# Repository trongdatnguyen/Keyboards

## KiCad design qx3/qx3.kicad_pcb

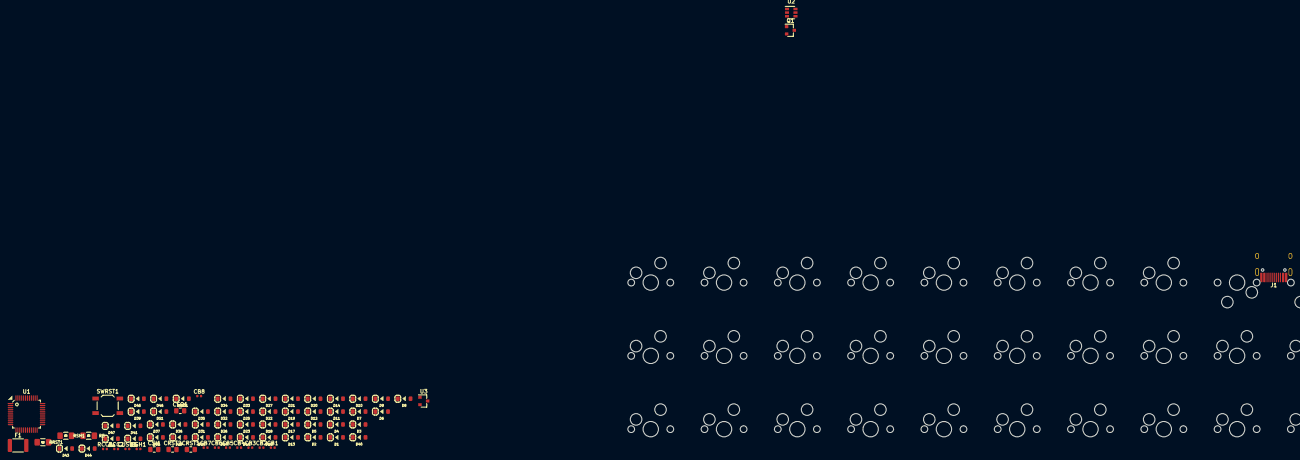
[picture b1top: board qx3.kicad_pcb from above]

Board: 2 copper layers, 121 parts (0 on the bottom side), 73 nets, no tracks yet.

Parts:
CB1: 1uF; C_0402_1005Metric
CB2: 10n; C_0402_1005Metric
CB3, CB5, CB8: 100n; C_0402_1005Metric
CB4, CB6: 4.7uF; C_0402_1005Metric
CB7: 100nF; C_0402_1005Metric
CRST1: 100uF; C_0805_2012Metric_Pad1.15x1.40mm_HandSolder
CRST2: 4.7nF; C_0805_2012Metric_Pad1.15x1.40mm_HandSolder
CSH1: 4.7nF; C_0402_1005Metric
CSI1: 10n; C_0805_2012Metric_Pad1.15x1.40mm_HandSolder
CSO1: 1u; C_0805_2012Metric_Pad1.15x1.40mm_HandSolder
CUSB1: 100n; C_0402_1005Metric
D1, D2, D3, D4, D5, D6, D7, D8, D9, D10, D11, D12, D13, D14, D15, D16, D17, D18, D19, D20, D21, D22, D23, D24, D25, D26, D27, D28, D29, D30, D31, D32, D33, D34, D35, D36, D37, D38, D39, D40, D41, D42, D43, D44, D45, D46: 1N4148; D_SOD-123
D47: D_TVS; D_SOD-123
DRST1: 1N4148; D_SOD-123
DS1: 1N4148; D_SOD-123
F1: Polyfuse_Small; Fuse_1812_4532
J1: TYPE-C-31-M12_13; HRO-TYPE-C-31-M-12-HandSoldering
Q1: DTC123J; SOT-23
R5: 33kO; R_SMD_1206
RCC1, RCC2: 5.1k; R_0402_1005Metric
RRST1: 100k; R_SMD_1206
RSH1: 1M; R_SMD_1206
SW1: SHIFT▲; MXOnly-1.5U-Hotswap
SW2: CHAR; MXOnly-1U-Hotswap
SW3: ENTER; MXOnly-4U-Hotswap
SW4: JOB COMMAND; MXOnly-1.5U-Hotswap
SW5: ◀; MXOnly-1U-Hotswap
SW6: ▶; MXOnly-1U-Hotswap
SW7: INS; MXOnly-1U-Hotswap
SW8: (; MXOnly-1U-Hotswap
SW9: ); MXOnly-1U-Hotswap
SW10: .; MXOnly-1U-Hotswap
SW11: _; MXOnly-1U-Hotswap
SW12: !; MXOnly-1U-Hotswap
SW13: ?; MXOnly-1U-Hotswap
SW14: &; MXOnly-1U-Hotswap
SW15: F1; MXOnly-1U-Hotswap
SW16: F2; MXOnly-1U-Hotswap
SW17: U; MXOnly-1U-Hotswap
SW18: V; MXOnly-1U-Hotswap
SW19: W; MXOnly-1U-Hotswap
SW20: X; MXOnly-1U-Hotswap
SW21: Y; MXOnly-1U-Hotswap
SW22: Z; MXOnly-1U-Hotswap
SW23: +; MXOnly-1U-Hotswap
SW24: -; MXOnly-1U-Hotswap
SW25: *; MXOnly-1U-Hotswap
SW26: /; MXOnly-1U-Hotswap
SW27: K; MXOnly-1U-Hotswap
SW28: L; MXOnly-1U-Hotswap
SW29: M; MXOnly-1U-Hotswap
SW30: N; MXOnly-1U-Hotswap
SW31: O; MXOnly-1U-Hotswap
SW32: P; MXOnly-1U-Hotswap
SW33: Q; MXOnly-1U-Hotswap
SW34: R; MXOnly-1U-Hotswap
SW35: S; MXOnly-1U-Hotswap
SW36: T; MXOnly-1U-Hotswap
SW37: A; MXOnly-1U-Hotswap
SW38: B; MXOnly-1U-Hotswap
SW39: C; MXOnly-1U-Hotswap
SW40: D; MXOnly-1U-Hotswap
SW41: E; MXOnly-1U-Hotswap
SW42: F; MXOnly-1U-Hotswap
SW43: G; MXOnly-1U-Hotswap
SW44: H; MXOnly-1U-Hotswap
SW45: I; MXOnly-1U-Hotswap
SW46: J; MXOnly-1U-Hotswap
SWRST1: SW_PUSH; SW_SPST_TL3342
U1: STM32F072-LQFP48; LQFP-48_7x7mm_P0.5mm
U2: USBLC6-2SC6; SOT-23-6
U3: MCP1700-3302E_SOT23; SOT-23

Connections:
3.3V: CB1.2, CB2.2, CB3.2, CB4.2, CB5.2, CB6.2, CB7.2, CB8.2, U1.1, U1.9, U1.24, U1.36, U1.48
5V: CSI1.1, D47.1, DS1.1, F1.1, U3.3
+3V3: CSO1.1, DS1.2, SWRST1.1, U3.2
BOOT0: CRST1.1, R5.1, RRST1.1, U1.44
Col1: SW1.1, SW7.1, SW17.1, SW27.1, SW37.1, U1.13
Col2: SW2.1, SW8.1, SW18.1, SW28.1, SW38.1, U1.14
Col3: SW9.1, SW19.1, SW29.1, SW39.1, U1.15
Col4: SW10.1, SW20.1, SW30.1, SW40.1, U1.16
Col5: SW11.1, SW21.1, SW31.1, SW41.1, U1.17
Col6: SW3.1, SW12.1, SW22.1, SW32.1, SW42.1, U1.18
Col7: SW13.1, SW23.1, SW33.1, SW43.1, U1.19
Col8: SW4.1, SW14.1, SW24.1, SW34.1, SW44.1, U1.20
Col9: SW5.1, SW15.1, SW25.1, SW35.1, SW45.1, U1.21
Col10: SW6.1, SW16.1, SW26.1, SW36.1, SW46.1, U1.22
D+: U1.33, U2.3
D-: U1.32, U2.1
GND: CB1.1, CB2.1, CB3.1, CB4.1, CB5.1, CB6.1, CB7.1, CB8.1, CRST1.2, CRST2.1, CSH1.2, CSI1.2, CSO1.2, CUSB1.1, D47.2, Q1.2, RCC1.1, RCC2.1, RRST1.2, RSH1.2, U1.8, U1.23, U1.35, U1.47, U2.2, U3.1
NRST: CRST2.2, Q1.3, U1.7
unnamed: CSH1.1, RSH1.1
unnamed: D1.2, SW1.2
unnamed: D2.2, SW2.2
unnamed: D3.2, SW3.2
unnamed: D4.2, SW4.2
unnamed: D5.2, SW5.2
unnamed: D6.2, SW6.2
unnamed: D7.2, SW7.2
unnamed: D8.2, SW8.2
unnamed: D9.2, SW9.2
unnamed: D10.2, SW10.2
unnamed: D11.2, SW11.2
unnamed: D12.2, SW12.2
unnamed: D13.2, SW13.2
unnamed: D14.2, SW14.2
unnamed: D15.2, SW15.2
unnamed: D16.2, SW16.2
unnamed: D17.2, SW17.2
unnamed: D18.2, SW18.2
unnamed: D19.2, SW19.2
unnamed: D20.2, SW20.2
unnamed: D21.2, SW21.2
unnamed: D22.2, SW22.2
unnamed: D23.2, SW23.2
unnamed: D24.2, SW24.2
unnamed: D25.2, SW25.2
unnamed: D26.2, SW26.2
unnamed: D27.2, SW27.2
unnamed: D28.2, SW28.2
unnamed: D29.2, SW29.2
unnamed: D30.2, SW30.2
unnamed: D31.2, SW31.2
unnamed: D32.2, SW32.2
unnamed: D33.2, SW33.2
unnamed: D34.2, SW34.2
unnamed: D35.2, SW35.2
unnamed: D36.2, SW36.2
unnamed: D37.2, SW37.2
unnamed: D38.2, SW38.2
unnamed: D39.2, SW39.2
unnamed: D40.2, SW40.2
unnamed: D41.2, SW41.2
unnamed: D42.2, SW42.2
unnamed: D43.2, SW43.2
unnamed: D44.2, SW44.2
unnamed: D45.2, SW45.2
unnamed: D46.2, SW46.2
unnamed: DRST1.1, R5.2
unnamed: DRST1.2, Q1.1, SWRST1.2
Row1: D1.1, D2.1, D3.1, D4.1, D5.1, D6.1, U1.2
Row2: D7.1, D8.1, D9.1, D10.1, D11.1, D12.1, D13.1, D14.1, D15.1, D16.1, U1.3
Row3: D17.1, D18.1, D19.1, D20.1, D21.1, D22.1, D23.1, D24.1, D25.1, D26.1, U1.4
Row4: D27.1, D28.1, D29.1, D30.1, D31.1, D32.1, D33.1, D34.1, D35.1, D36.1, U1.5
Row5: D37.1, D38.1, D39.1, D40.1, D41.1, D42.1, D43.1, D44.1, D45.1, D46.1, U1.6
VBUS: CUSB1.2, F1.2, U2.5

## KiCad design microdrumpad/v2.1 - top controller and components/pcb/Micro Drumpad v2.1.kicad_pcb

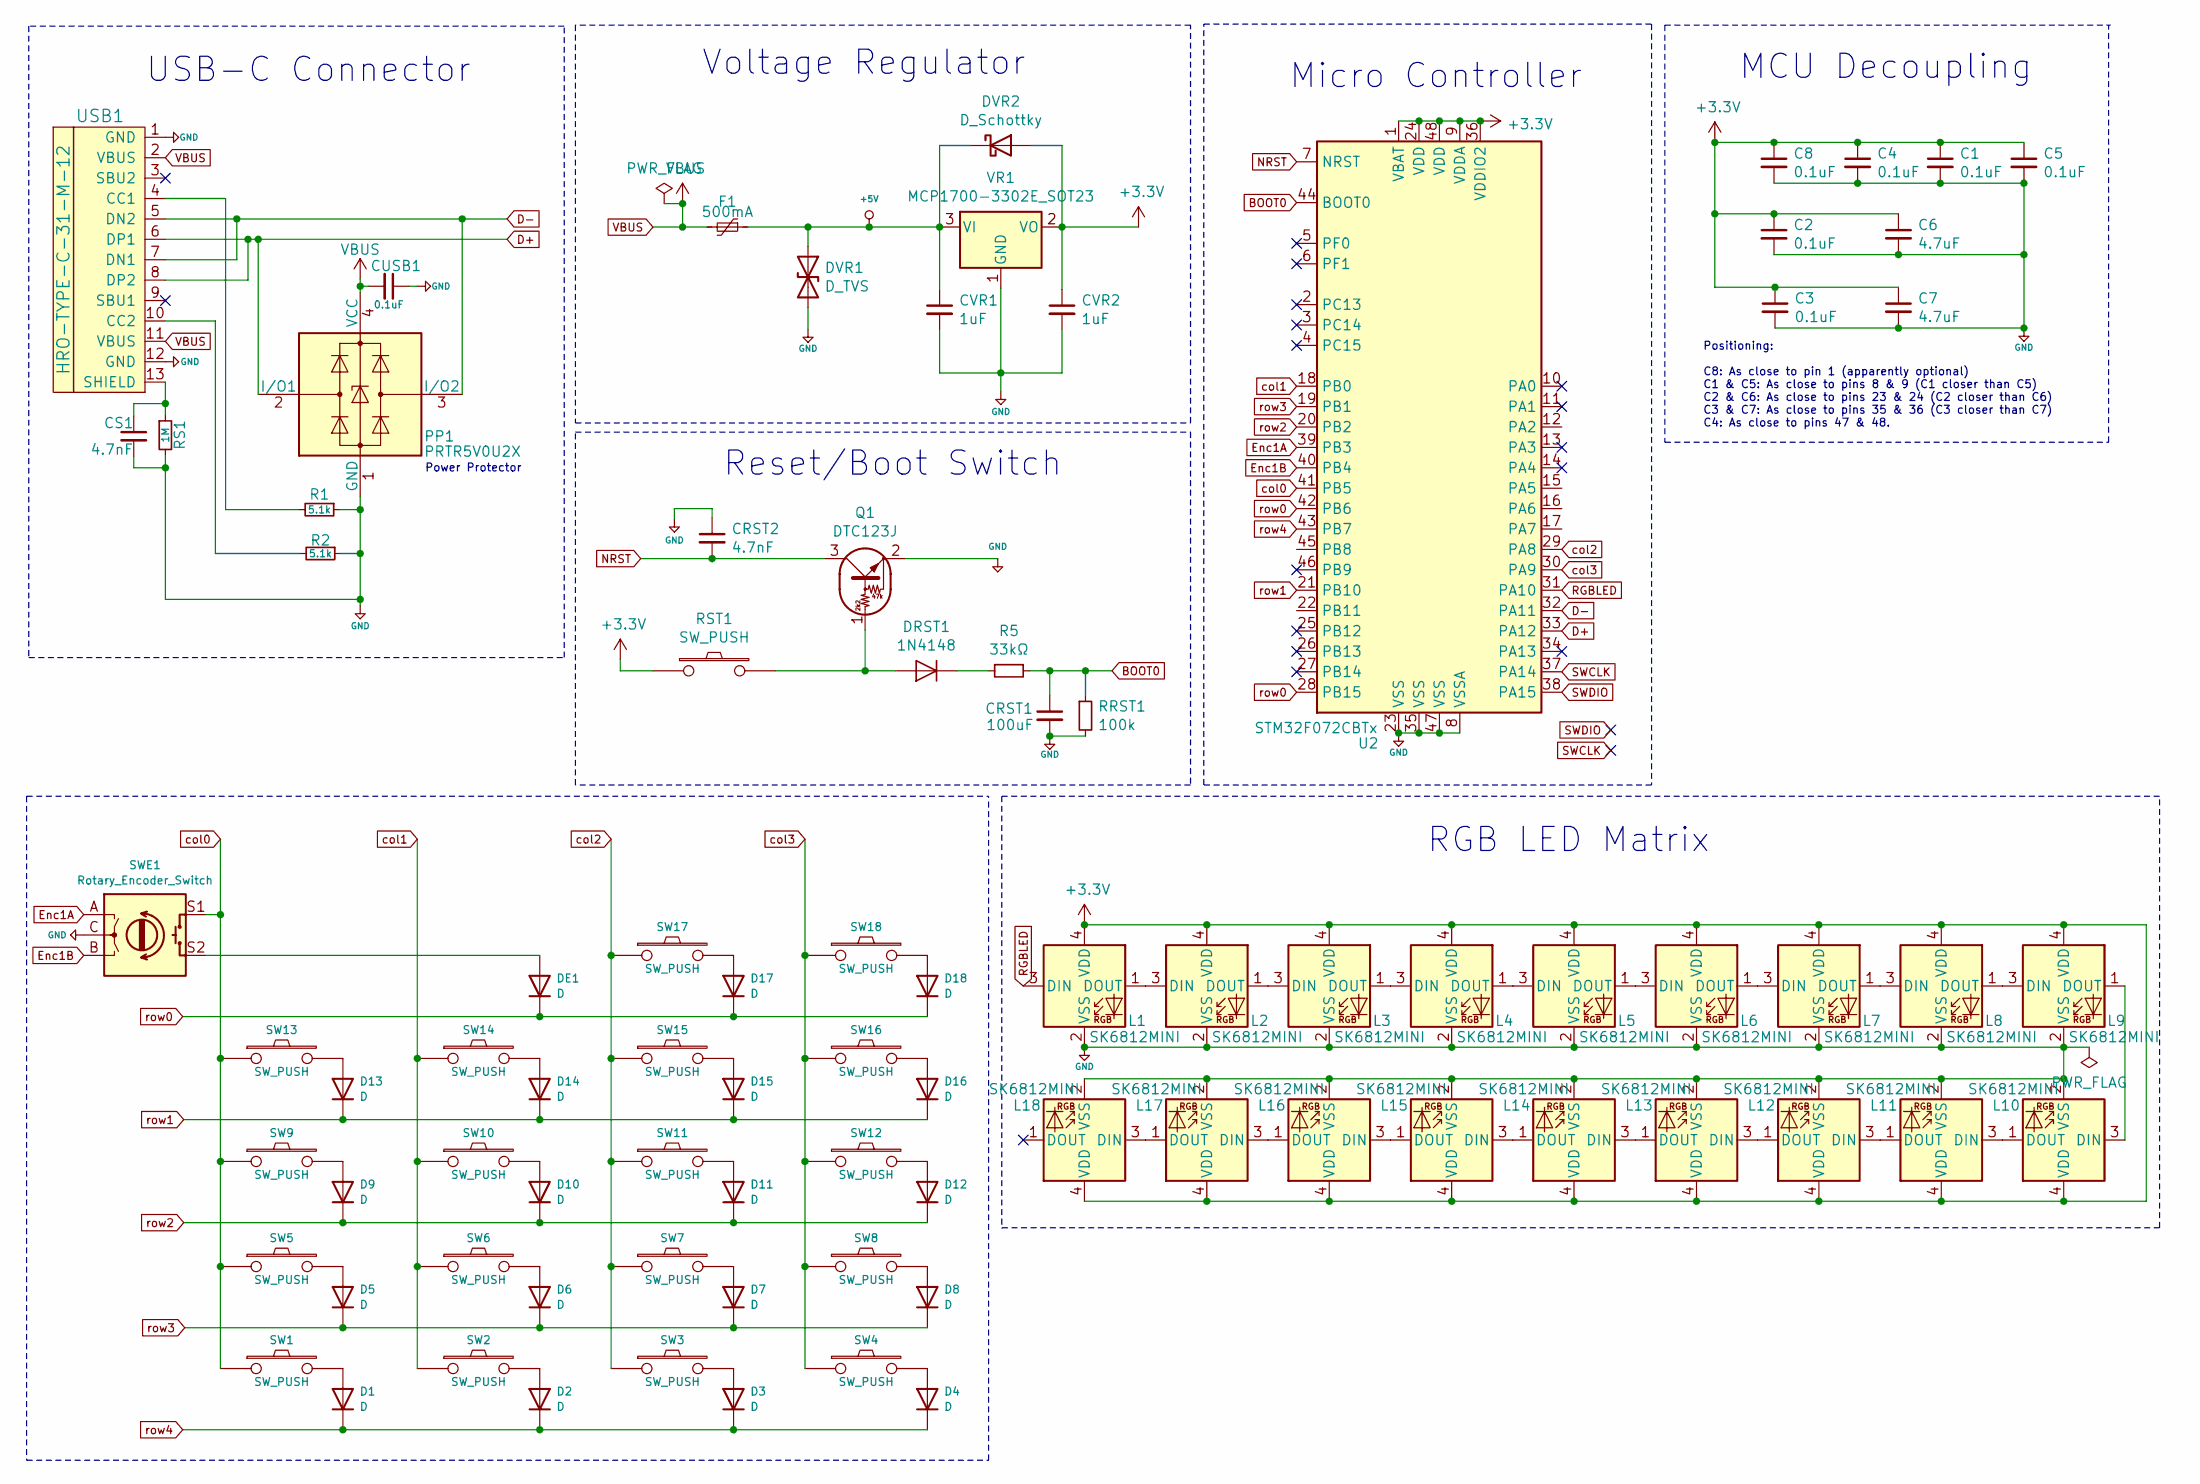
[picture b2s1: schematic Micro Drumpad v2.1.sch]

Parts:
C1, C2, C3, C4, C5, C8: 0.1uF; C_0805_2012Metric
C6, C7: 4.7uF; C_0805_2012Metric
CRST1: 100uF; C_0805_2012Metric
CRST2: 4.7nF; C_0805_2012Metric
CS1: 4.7nF; C_0805_2012Metric
CUSB1: 0.1uF; C_0805_2012Metric
CVR1, CVR2: 1uF; C_0805_2012Metric
D1, D2, D3, D4, D5, D6, D7, D8, D9, D10, D11, D12, D13, D14, D15, D16, D17, D18: D; D_SOD-123
DE1: D; D_SOD-123
DRST1: 1N4148; D_DO-35_SOD27_P7.62mm_Horizontal
DVR1: D_TVS; D_SOD-123
DVR2: D_Schottky; D_SOD-123
F1: 500mA; Fuse_1206_3216Metric
L1, L2, L3, L4, L5, L6, L7, L8, L9, L10, L11, L12, L13, L14, L15, L16, L17, L18: SK6812MINI; LED_SK6812MINI_PLCC4_3.5x3.5mm_P1.75mm
PP1: PRTR5V0U2X; SOT-143
Q1: DTC123J; SOT-23
R1, R2: 5.1k; R_0805_2012Metric
R5: 33kΩ; R_0805_2012Metric
RRST1: 100k; R_0805_2012Metric
RS1: 1M; R_0805_2012Metric
RST1: SW_PUSH; SW_SPST_TL3342
SW1, SW2, SW3, SW4, SW5, SW6, SW7, SW8, SW9, SW10, SW11, SW12, SW13, SW14, SW15, SW16, SW17, SW18: SW_PUSH; MXOnly-1U-Hotswap
SWE1: Rotary_Encoder_Switch; RotaryEncoder_Alps_EC11E-Switch_Vertical_H20mm
U2: STM32F072CBTx; LQFP-48_7x7mm_P0.5mm
USB1: HRO-TYPE-C-31-M-12
VR1: MCP1700-3302E_SOT23; SOT-23

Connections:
+3V3: C1.1, C2.1, C3.1, C4.1, C5.1, C6.1, C7.1, C8.1, CVR2.1, DVR2.2 (A), L1.4 (VDD), L2.4 (VDD), L3.4 (VDD), L4.4 (VDD), L5.4 (VDD), L6.4 (VDD), L7.4 (VDD), L8.4 (VDD), L9.4 (VDD), L10.4 (VDD), L11.4 (VDD), L12.4 (VDD), L13.4 (VDD), L14.4 (VDD), L15.4 (VDD), L16.4 (VDD), L17.4 (VDD), L18.4 (VDD), RST1.1, U2.1 (VBAT), U2.9 (VDDA), U2.24 (VDD), U2.36 (VDDIO2), U2.48 (VDD), VR1.2 (VO)
BOOT0: CRST1.1, R5.1, RRST1.1, U2.44 (BOOT0)
D+: PP1.2 (I/O1), U2.33 (PA12), USB1.6 (DP1), USB1.8 (DP2)
D-: PP1.3 (I/O2), U2.32 (PA11), USB1.5 (DN2), USB1.7 (DN1)
Enc1A: SWE1.A, U2.39 (PB3)
Enc1B: SWE1.B, U2.40 (PB4)
NRST: CRST2.2, Q1.3 (C), U2.7 (NRST)
unnamed: CS1.1, RS1.1, USB1.13 (SHIELD)
unnamed: D1.2 (A), SW1.2
unnamed: D2.2 (A), SW2.2
unnamed: D3.2 (A), SW3.2
unnamed: D4.2 (A), SW4.2
unnamed: D5.2 (A), SW5.2
unnamed: D6.2 (A), SW6.2
unnamed: D7.2 (A), SW7.2
unnamed: D8.2 (A), SW8.2
unnamed: D9.2 (A), SW9.2
unnamed: D10.2 (A), SW10.2
unnamed: D11.2 (A), SW11.2
unnamed: D12.2 (A), SW12.2
unnamed: D13.2 (A), SW13.2
unnamed: D14.2 (A), SW14.2
unnamed: D15.2 (A), SW15.2
unnamed: D16.2 (A), SW16.2
unnamed: D17.2 (A), SW17.2
unnamed: D18.2 (A), SW18.2
unnamed: DE1.2 (A), SWE1.S2
unnamed: DRST1.1 (K), R5.2
unnamed: DRST1.2 (A), Q1.1 (B), RST1.2
unnamed: L1.1 (DOUT), L2.3 (DIN)
unnamed: L2.1 (DOUT), L3.3 (DIN)
unnamed: L3.1 (DOUT), L4.3 (DIN)
unnamed: L4.1 (DOUT), L5.3 (DIN)
unnamed: L5.1 (DOUT), L6.3 (DIN)
unnamed: L6.1 (DOUT), L7.3 (DIN)
unnamed: L7.1 (DOUT), L8.3 (DIN)
unnamed: L8.1 (DOUT), L9.3 (DIN)
unnamed: L10.1 (DOUT), L11.3 (DIN)
unnamed: L9.1 (DOUT), L10.3 (DIN)
unnamed: L11.1 (DOUT), L12.3 (DIN)
unnamed: L12.1 (DOUT), L13.3 (DIN)
unnamed: L13.1 (DOUT), L14.3 (DIN)
unnamed: L14.1 (DOUT), L15.3 (DIN)
unnamed: L15.1 (DOUT), L16.3 (DIN)
unnamed: L16.1 (DOUT), L17.3 (DIN)
unnamed: L17.1 (DOUT), L18.3 (DIN)
unnamed: R1.2, USB1.4 (CC1)
unnamed: R2.2, USB1.10 (CC2)
RGBLED: L1.3 (DIN), U2.31 (PA10)
SWCLK: U2.37 (PA14)
SWDIO: U2.38 (PA15)
VBUS: CUSB1.2, F1.2, PP1.4 (VCC), USB1.2 (VBUS), USB1.11 (VBUS)
col0: SW1.1, SW5.1, SW9.1, SW13.1, SWE1.S1, U2.41 (PB5)
col1: SW2.1, SW6.1, SW10.1, SW14.1, U2.18 (PB0)
col2: SW3.1, SW7.1, SW11.1, SW15.1, SW17.1, U2.29 (PA8)
col3: SW4.1, SW8.1, SW12.1, SW16.1, SW18.1, U2.30 (PA9)
row0: D17.1 (K), D18.1 (K), DE1.1 (K), U2.28 (PB15), U2.42 (PB6)
row1: D13.1 (K), D14.1 (K), D15.1 (K), D16.1 (K), U2.21 (PB10)
row2: D9.1 (K), D10.1 (K), D11.1 (K), D12.1 (K), U2.20 (PB2)
row3: D5.1 (K), D6.1 (K), D7.1 (K), D8.1 (K), U2.19 (PB1)
row4: D1.1 (K), D2.1 (K), D3.1 (K), D4.1 (K), U2.43 (PB7)

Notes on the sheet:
MCU Decoupling
Reset/Boot Switch
Micro Controller
Positioning: C8: As close to pin 1 (apparently optional) C1 & C5: As close to pins 8 & 9 (C1 closer than C5) C2 & C6: As close to pins 23 & 24 (C2 closer than C6) C3 & C7: As close to pins 35 & 36 (C3 closer than C7) C4: As close to pins 47 & 48.
Voltage Regulator
USB-C Connector
Power Protector
RGB LED Matrix

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
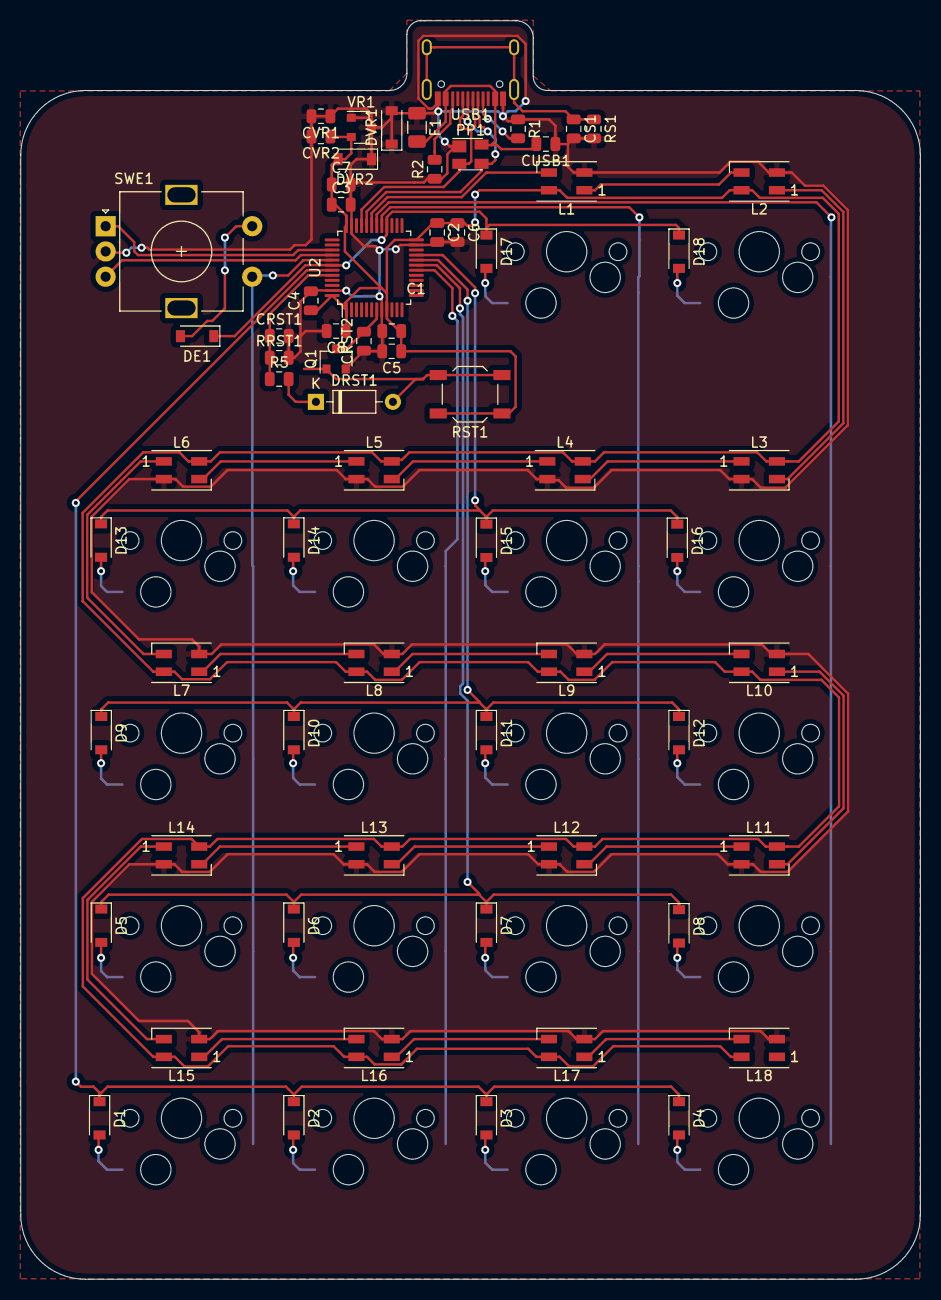
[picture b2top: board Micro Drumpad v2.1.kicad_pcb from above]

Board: 2 copper layers, 89.0 x 124.5 mm, 86 parts (0 on the bottom side), 60 nets.

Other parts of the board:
H1: MountingHole; MountingHole_2.2mm_M2_DIN965

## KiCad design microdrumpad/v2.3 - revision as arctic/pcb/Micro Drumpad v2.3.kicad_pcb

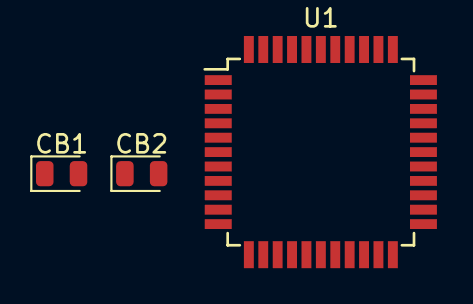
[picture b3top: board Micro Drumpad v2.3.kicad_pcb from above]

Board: 2 copper layers, 3 parts (0 on the bottom side), 2 nets, no tracks yet.

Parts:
CB1, CB2: 10n; D_0805_2012Metric
U1: STM32F072-LQFP48; TQFP-44_10x10mm_P0.8mm

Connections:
3.3V: CB1.2, CB2.2, U1.10
+5V: CB1.1, CB2.1, U1.9

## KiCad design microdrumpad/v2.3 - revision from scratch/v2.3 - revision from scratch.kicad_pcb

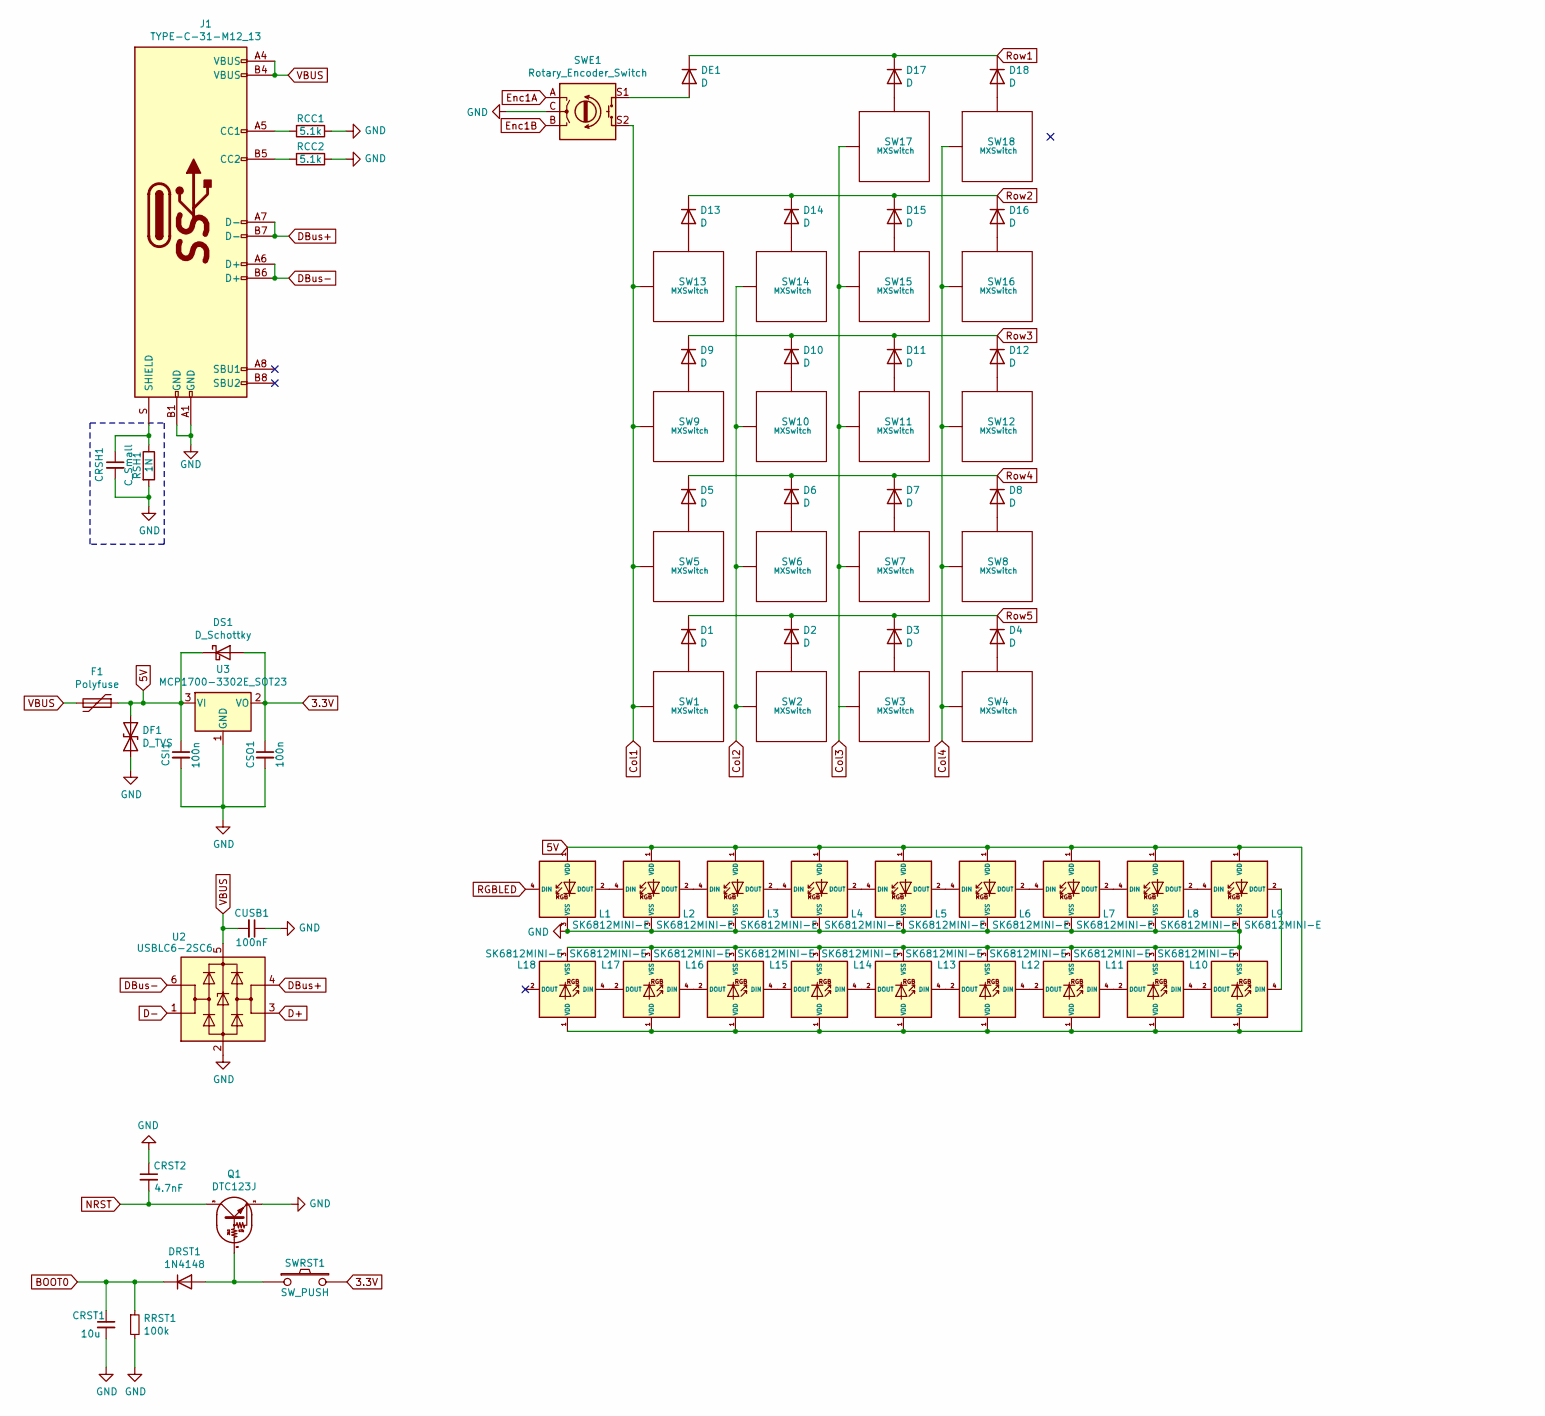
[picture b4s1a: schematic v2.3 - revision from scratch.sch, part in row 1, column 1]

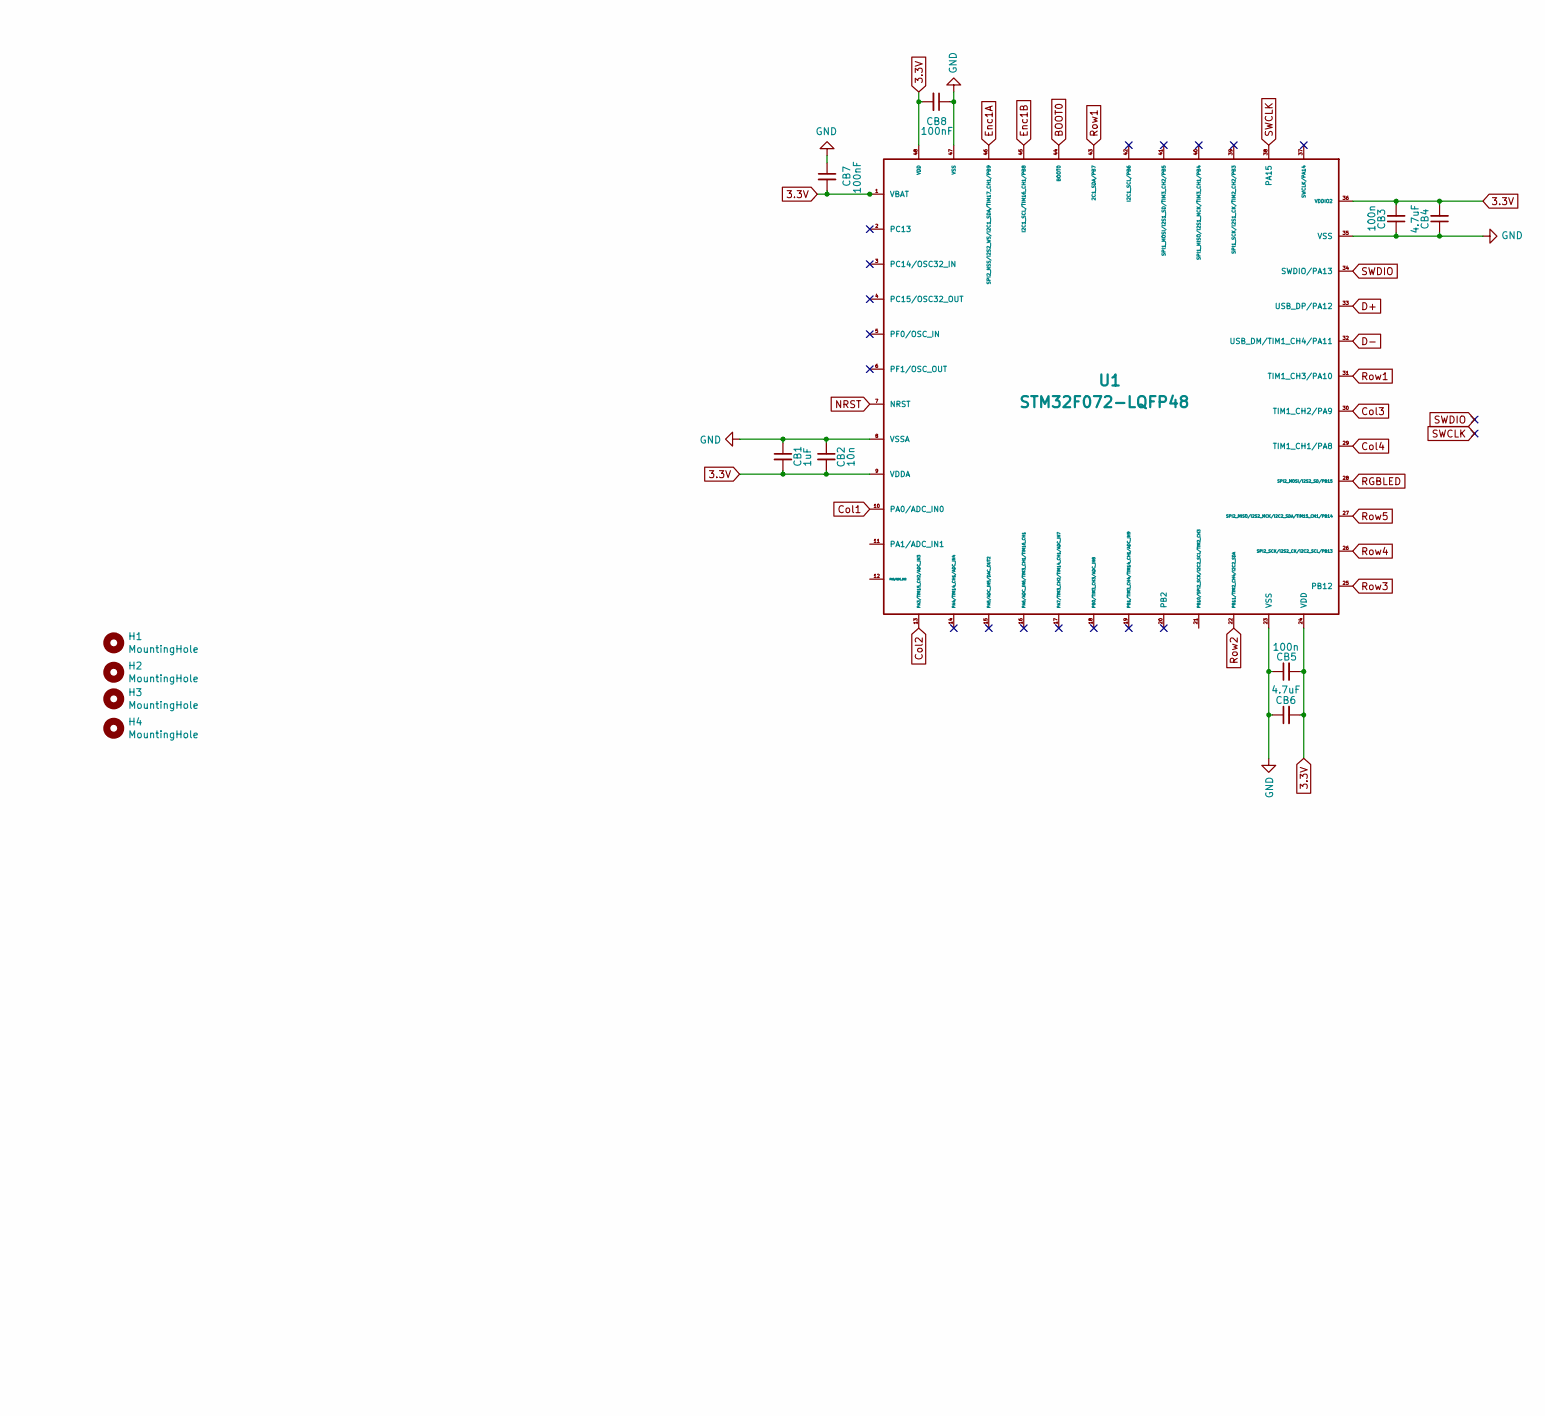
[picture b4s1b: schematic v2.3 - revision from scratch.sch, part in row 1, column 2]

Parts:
CB1: 1uF; C_0805_2012Metric
CB2: 10n; C_0805_2012Metric
CB3, CB5: 100n; C_0805_2012Metric
CB4, CB6: 4.7uF; C_0805_2012Metric
CB7, CB8: 100nF; C_0805_2012Metric
CRSH1: C_Small; C_0805_2012Metric
CRST1: 10u; C_0805_2012Metric
CRST2: 4.7nF; C_0805_2012Metric
CSI1: 100n; C_0805_2012Metric
CSO1: 100n; C_0805_2012Metric
CUSB1: 100nF; D_SOD-123
D1, D2, D3, D4, D5, D6, D7, D8, D9, D10, D11, D12, D13, D14, D15, D16, D17, D18: D; D_SOD-123
DE1: D; D_SOD-123
DF1: D_TVS; D_SOD-123
DRST1: 1N4148; D_DO-35_SOD27_P7.62mm
DS1: D_Schottky; D_SOD-123
F1: Polyfuse; Fuse_0805_2012Metric_Pad1.15x1.40mm_HandSolder
H1: MountingHole; Mounting_Hole_Oval_2.5x8mm
H2: MountingHole; halfSideHole
H3: MountingHole; MoutingHole_Oval_7mm_5.0x2.5mm
H4: MountingHole; MoutingHole_Oval_Poker_7mm_5.0x2.5mm
J1: TYPE-C-31-M12_13; TYPE-C-31-M-12
L1, L2, L3, L4, L5, L6, L7, L8, L9, L10, L11, L12, L13, L14, L15, L16, L17, L18: SK6812MINI-E; SK6812-MINI-E
Q1: DTC123J; SOT-23
RCC1, RCC2: 5.1k; R_SMD_1206
RRST1: 100k; R_SMD_1206
RSH1: 1N; R_SMD_1206
SW1, SW2, SW3, SW4, SW5, SW6, SW7, SW8, SW9, SW10, SW11, SW12, SW13, SW14, SW15, SW16, SW17, SW18: MXSwitch; MXOnly-1U-Hotswap
SWE1: Rotary_Encoder_Switch; RotaryEncoder_Alps_EC11E-Switch_Vertical_H20mm
SWRST1: SW_PUSH; SW_SPST_TL3342
U1: STM32F072-LQFP48; LQFP-48_7x7mm_P0.5mm
U2: USBLC6-2SC6; SOT-23-6
U3: MCP1700-3302E_SOT23; SOT-23

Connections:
3.3V: CB1.2, CB2.2, CB3.2, CB4.2, CB5.2, CB6.2, CB7.2, CB8.2, CSO1.1, DS1.2 (A), SWRST1.2, U1.1 (VBAT), U1.9 (VDDA), U1.24 (VDD), U1.36 (VDDIO2), U1.48 (VDD), U3.2 (VO)
5V: CSI1.1, DF1.2 (A2), DS1.1 (K), F1.1, L1.1 (VDD), L2.1 (VDD), L3.1 (VDD), L4.1 (VDD), L5.1 (VDD), L6.1 (VDD), L7.1 (VDD), L8.1 (VDD), L9.1 (VDD), L10.1 (VDD), L11.1 (VDD), L12.1 (VDD), L13.1 (VDD), L14.1 (VDD), L15.1 (VDD), L16.1 (VDD), L17.1 (VDD), L18.1 (VDD), U3.3 (VI)
BOOT0: CRST1.1, DRST1.1 (K), RRST1.1, U1.44 (BOOT0)
Col1: SW1.1 (Col), SW5.1 (Col), SW9.1 (Col), SW13.1 (Col), SWE1.S2, U1.10 (PA0/ADC_IN0)
Col2: SW2.1 (Col), SW6.1 (Col), SW10.1 (Col), SW14.1 (Col), U1.13 (PA3/TIM15_CH2/ADC_IN3)
Col3: SW3.1 (Col), SW7.1 (Col), SW11.1 (Col), SW15.1 (Col), SW17.1 (Col), U1.30 (TIM1_CH2/PA9)
Col4: SW4.1 (Col), SW8.1 (Col), SW12.1 (Col), SW16.1 (Col), SW18.1 (Col), U1.29 (TIM1_CH1/PA8)
D+: U1.33 (USB_DP/PA12), U2.3 (I/O2)
D-: U1.32 (USB_DM/TIM1_CH4/PA11), U2.1 (I/O1)
DBus+: J1.A7 (D-), J1.B7 (D-), U2.4 (I/O2)
DBus-: J1.A6 (D+), J1.B6 (D+), U2.6 (I/O1)
Enc1A: SWE1.A, U1.46 (SPI2_NSS/I2S2_WS/I2C1_SDA/TIM17_CH1/PB9)
Enc1B: SWE1.B, U1.45 (I2C1_SCL/TIM16_CH1/PB8)
GND: CB1.1, CB2.1, CB3.1, CB4.1, CB5.1, CB6.1, CB7.1, CB8.1, CRSH1.2, CRST1.2, CRST2.1, CSI1.2, CSO1.2, CUSB1.1, DF1.1 (A1), J1.A1 (GND), J1.B1 (GND), L1.3 (VSS), L2.3 (VSS), L3.3 (VSS), L4.3 (VSS), L5.3 (VSS), L6.3 (VSS), L7.3 (VSS), L8.3 (VSS), L9.3 (VSS), L10.3 (VSS), L11.3 (VSS), L12.3 (VSS), L13.3 (VSS), L14.3 (VSS), L15.3 (VSS), L16.3 (VSS), L17.3 (VSS), L18.3 (VSS), Q1.2 (E), RCC1.1, RCC2.1, RRST1.2, RSH1.2, SWE1.C, U1.8 (VSSA), U1.23 (VSS), U1.35 (VSS), U1.47 (VSS), U2.2 (GND), U3.1 (GND)
NRST: CRST2.2, Q1.3 (C), U1.7 (NRST)
unnamed: CRSH1.1, J1.S (SHIELD), RSH1.1
unnamed: D1.2 (A), SW1.2 (Row)
unnamed: D2.2 (A), SW2.2 (Row)
unnamed: D3.2 (A), SW3.2 (Row)
unnamed: D4.2 (A), SW4.2 (Row)
unnamed: D5.2 (A), SW5.2 (Row)
unnamed: D6.2 (A), SW6.2 (Row)
unnamed: D7.2 (A), SW7.2 (Row)
unnamed: D8.2 (A), SW8.2 (Row)
unnamed: D9.2 (A), SW9.2 (Row)
unnamed: D10.2 (A), SW10.2 (Row)
unnamed: D11.2 (A), SW11.2 (Row)
unnamed: D12.2 (A), SW12.2 (Row)
unnamed: D13.2 (A), SW13.2 (Row)
unnamed: D14.2 (A), SW14.2 (Row)
unnamed: D15.2 (A), SW15.2 (Row)
unnamed: D16.2 (A), SW16.2 (Row)
unnamed: D17.2 (A), SW17.2 (Row)
unnamed: D18.2 (A), SW18.2 (Row)
unnamed: DE1.2 (A), SWE1.S1
unnamed: DRST1.2 (A), Q1.1 (B), SWRST1.1
unnamed: J1.A5 (CC1), RCC1.2
unnamed: J1.B5 (CC2), RCC2.2
unnamed: L1.2 (DOUT), L2.4 (DIN)
unnamed: L2.2 (DOUT), L3.4 (DIN)
unnamed: L3.2 (DOUT), L4.4 (DIN)
unnamed: L4.2 (DOUT), L5.4 (DIN)
unnamed: L5.2 (DOUT), L6.4 (DIN)
unnamed: L6.2 (DOUT), L7.4 (DIN)
unnamed: L7.2 (DOUT), L8.4 (DIN)
unnamed: L8.2 (DOUT), L9.4 (DIN)
unnamed: L10.2 (DOUT), L11.4 (DIN)
unnamed: L9.2 (DOUT), L10.4 (DIN)
unnamed: L11.2 (DOUT), L12.4 (DIN)
unnamed: L12.2 (DOUT), L13.4 (DIN)
unnamed: L13.2 (DOUT), L14.4 (DIN)
unnamed: L14.2 (DOUT), L15.4 (DIN)
unnamed: L15.2 (DOUT), L16.4 (DIN)
unnamed: L16.2 (DOUT), L17.4 (DIN)
unnamed: L17.2 (DOUT), L18.4 (DIN)
RGBLED: L1.4 (DIN), U1.28 (SPI2_MOSI/I2S2_SD/PB15)
Row1: D17.1 (K), D18.1 (K), DE1.1 (K), U1.31 (TIM1_CH3/PA10), U1.43 (2C1_SDA/PB7)
Row2: D13.1 (K), D14.1 (K), D15.1 (K), D16.1 (K), U1.22 (PB11/TIM2_CH4/I2C2_SDA)
Row3: D9.1 (K), D10.1 (K), D11.1 (K), D12.1 (K), U1.25 (PB12)
Row4: D5.1 (K), D6.1 (K), D7.1 (K), D8.1 (K), U1.26 (SPI2_SCK/I2S2_CK/I2C2_SCL/PB13)
Row5: D1.1 (K), D2.1 (K), D3.1 (K), D4.1 (K), U1.27 (SPI2_MISO/I2S2_MCK/I2C2_SDA/TIM15_CH1/P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)
SWCLK: U1.38 (PA15)
SWDIO: U1.34 (SWDIO/PA13)
VBUS: CUSB1.2, F1.2, J1.A4 (VBUS), J1.B4 (VBUS), U2.5 (VBUS)

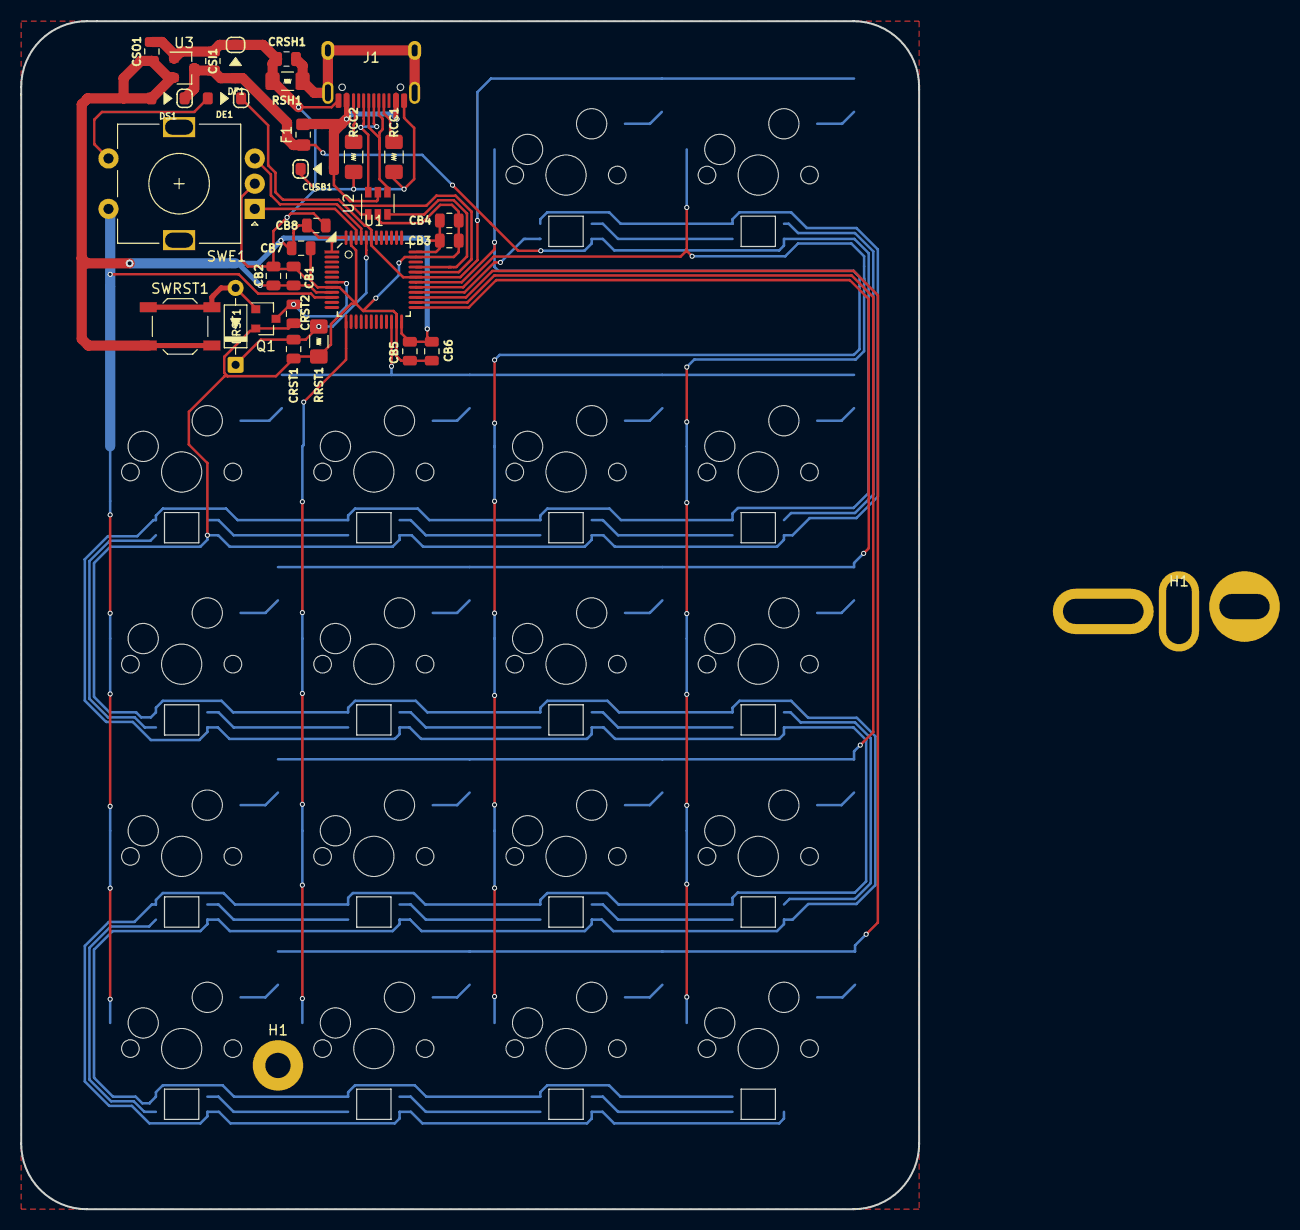
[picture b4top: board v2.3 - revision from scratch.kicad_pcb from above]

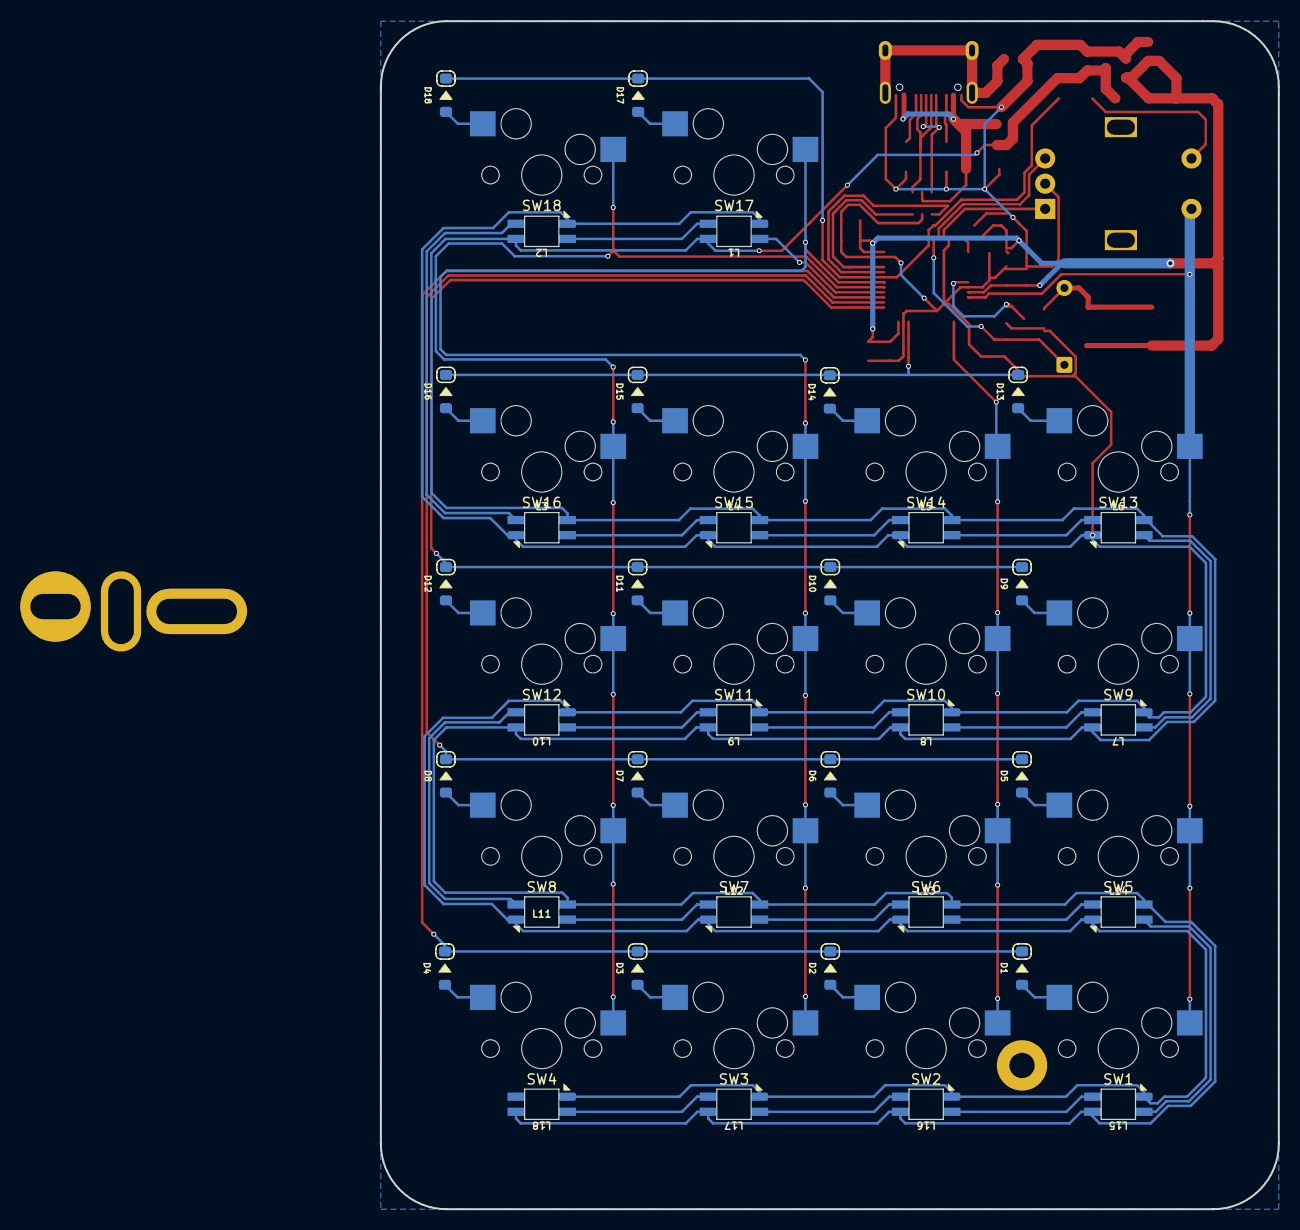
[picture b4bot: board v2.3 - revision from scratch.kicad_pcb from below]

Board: 2 copper layers, 89.0 x 117.8 mm, 88 parts (36 on the bottom side), 62 nets.

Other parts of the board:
H1#2: MountingHole; MountingHole_2.5mm_Pad

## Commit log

2020-08-18 v1.0
2020-08-18 v2.0
2020-08-18 minor update
2020-08-18 my keyboard archive
2020-08-26 Update QX3
